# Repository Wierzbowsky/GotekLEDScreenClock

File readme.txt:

--------------------------------------------------------------------------------
Clock with calendar from Gotek's LED screen parts
Copyright (c) 2022-2023 Wierzbowsky [RBSC]
Version 1.0.0005
--------------------------------------------------------------------------------

About
-----

This is the the self-made clock that was created from salvaged Gotek's 7-segment LED screen boards. The original Gotek
screen boards need to be dismantled and all parts (IC, screen, capacitor) are used to create a single or combined
indicator panel with the help of tiny circuit boards that can be joined together. These boards share all signals except
for DIO. Each DIO pin is connected to the corresponding pin of the Arduino Mini, Nano or Uno board. This particular clock
has 6 screens joined together.

The screens can display decimal and hexadecimal numbers with or without prepending zeroes, single digits and characters
at defined positions, all Latin alphabet and also several special characters (minus, plus, slash, etc). The original
Arduino library for the TM1651 chip created by Derek Cooper was almost completely rewritten and enriched with features.
A few subroutines from the library were imported into the .INO file to make things easier.

The Arduino board with the custom self-made firmware allows to set the time and date, select 3 brightness levels and also
to enable the auto-brightness mode. A user can enable the hourly beep during day hours and set the adjustment to slow
down or make the clock run faster. The total consumption of the clock with Arduino board is around 100mA, so powering it
up from a USB2 port is fine.

Assembling
----------

Take 6 orginal Gotek LED screen boards and desolder the LED screen, the controller chip and the capacitor. The solder the
chip, capacitor and the screen onto the small board (you can order it from jlcpcb.com factory using the provided Gerber
files).

Solder a 4-pin single row header to the right side of one assembled board. To make it easier, it's recommended to solder
the 4-pin header BEFORE soldering the screen. Cut the popping out pins of the pin header from the other side so that the
screen could be fully set onto the board.

Assemble the 2-row 3-column display from the 6 complete boards. Make sure that there's no gap between the screens. To join
the boards you can use U shaped pins cut from the pin headers. See the picture of the assembled screen for reference.

Connect power, ground and clock lines of each screens in a row together. Solder 3 wires between corresponding solder pads
of power, ground and clock signals of the upper row and the bottom row. See the picture of the assembled screen.

Finally, solder four 2-pin headers onto the DIO solder pads of each board. 

Connections
-----------

Connect each board's DIO pin to the digitap I/O pin of the Arduino Uno or Nano board. Please note thet the board has DIO
pads on each side, so please connect only ONE of them (one DIO signal for each screen). Connecting the DIO pins should be
done in the specific order so that the pin the the smallest number is connected to the leftmost screen.

In my setup the DIO pins are connected to the Arduino board the following way:

-------------------------
|---3---|---4---|---5---|
-------------------------
|---6---|---7---|---8---|
-------------------------

Connect the 3.3v power from the Arduino board to the 4-pin header's VCC pin. Connect the ground from the Arduino board to
the 4-pin header's GND pin. Connect the I/O pin 3 from the Arduino board to the 4-pin header's CLK pin (this is clock
signal). You can change the pin assignment in the source files if you wish. The current pin assignment is as follows:

Arduino		Clock board or beeper/button
--------------------------------------------
3.3v		VCC
GND		GND
 2		CLK
 3		DIO pin of screen 1
 4		DIO pin of screen 2
 5		DIO pin of screen 3
 6		DIO pin of screen 4
 7		DIO pin of screen 5
 8		DIO pin of screen 6
12		Beeper (optional)
13		Button
GND		Beeper's ground
GND             Button's ground

The piezo beeper is optional, but recommended. You can use a simple 2-pin beeper in a barrel-shaped case. It can be found
anywhere on AliExpress or Ebay. For example: https://www.ebay.com/itm/374210416844

Operation
---------

The clock is controlled by a single pushbutton. There are 3 types of commands that you can execute. A short pushdown (less
than 1 second push), a medium pushdown (over 1 second push) and a long pushdown (over 2 second push). It's all about timing.
Each operation is acknowledged by the clock with a beep of different frequency and duration if beep is enabled.

When the clock shows date and time, a short pushdown will change the brightness mode and disable the auto-brightness mode if
if was previously set. There are 3 different brightness levels to select manually. The auto-brightness uses only the dimmest
and the brightest levels.

The medium pushdown will allow to enter the settings mode (see below). The long pushdown switches on the auto-brightness
mode. The brightness will automatically change based on time of the day. From 8:00 to 20:00 high brightness is set,
otherwise low brightness is set.

The settings option can be selected by holding the pushbutton for over 1 second. In the settings mode a short pushdown will
change the value of hour, minute, second (reset to zero), day, month, year, select beep ON or beep OFF, select auto-brightness
ON of OFF, as well as allow to set the clock speed adjustment in the range of -15 to 15 (slow/fast). A short pushdown will
zero the value of seconds if seconds are blinking, for other values it will either switch them between ON or OFF or advance
the setting by 1. The medium pushdown will allow to select the setting that needs to be changed (hour, minute, day, etc.).
The currently selected value will blink. The selection is done in a loop, for example: second->minute->hour->second. The long
pushdown will switch to the next setup screen. That last screen of the setup will ask to press a button to start the clock
with the selected settings. The following setup screens are available in version 1.0.0005:

-> Set time -> Set date -> Set auto-brightness -> Set beep -> Set adjust -> Start clock

It may be tricky to change settings for the first time, but you will get used to it pretty fast.

Operation and test videos
-------------------------

You can see the videos of the clock's testing on Youtube:

 - https://www.youtube.com/watch?v=1-ujJE8o4cY
 - https://www.youtube.com/watch?v=EFognT4_trQ

IMPORTANT!
----------

I provide all files and information for free, without any liability (see the disclaimer.txt file). The provided information,
software or hardware must not be used for commercial purposes unless permitted by the owner. Producing a small amount of
bare boards for personal projects and selling the rest of the batch is allowed without the permission.

When the sources files are used to create alternative projects, please always mention the original source and the copyright!

Contact information
-------------------

The members of RBSC group Tnt23, Wierzbowsky, Pyhesty, Ptero, GreyWolf, SuperMax, VWarlock and DJS3000 can be contacted via the group's e-mail
address:

info@rbsc.su

The group's coordinator could be reached via this e-mail address:

admin@rbsc.su

The group's website can be found here:

https://rbsc.su/
https://rbsc.su/ru

The RBSC's hardware repository can be found here:

https://github.com/rbsc

The RBSC's 3D model repository can be found here:

https://www.thingiverse.com/groups/rbsc/things

-= ! MSX FOREVER ! =-

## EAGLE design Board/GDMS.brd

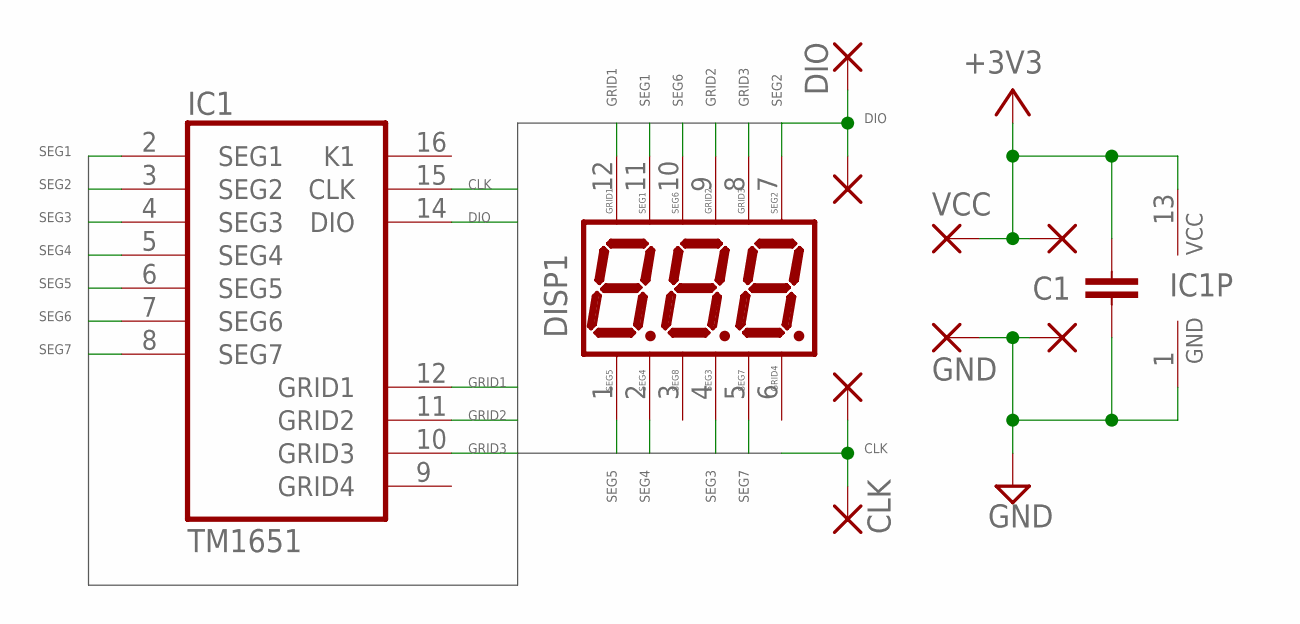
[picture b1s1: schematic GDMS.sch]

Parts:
C1: 100nF; C0805
DIS1: SP410312N; 3D7SEG
IC1: TM1651; SO16
P1: VCC; PADTH
P2, P4, P8, P9: PADTH
P3: GND; PADTH
P7: CLK; PADTH
P10: DIO; PADTH

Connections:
+3V3: C1.1, IC1.13 (VCC), P1.1, P2.1
CLK: IC1.15 (CLK), P7.1, P8.1
DIO: IC1.14 (DIO), P9.1, P10.1
GND: C1.2, IC1.1 (GND), P3.1, P4.1
GRID1: DIS1.12 (GRID1), IC1.12 (GRID1)
GRID2: DIS1.9 (GRID2), IC1.11 (GRID2)
GRID3: DIS1.8 (GRID3), IC1.10 (GRID3)
SEG1: DIS1.11 (SEG1), IC1.2 (SEG1)
SEG2: DIS1.7 (SEG2), IC1.3 (SEG2)
SEG3: DIS1.4 (SEG3), IC1.4 (SEG3)
SEG4: DIS1.2 (SEG4), IC1.5 (SEG4)
SEG5: DIS1.1 (SEG5), IC1.6 (SEG5)
SEG6: DIS1.10 (SEG6), IC1.7 (SEG6)
SEG7: DIS1.5 (SEG7), IC1.8 (SEG7)

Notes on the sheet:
DISP1

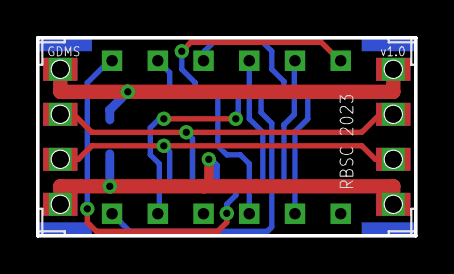
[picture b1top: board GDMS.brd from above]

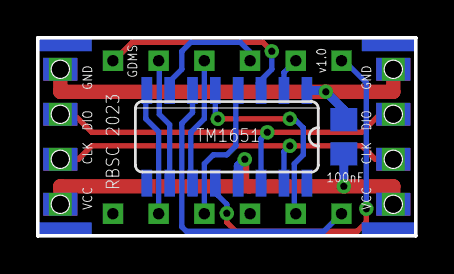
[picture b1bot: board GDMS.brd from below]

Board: 2 copper layers, 21.0 x 11.0 mm, 11 parts (2 on the bottom side), 14 nets.

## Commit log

2023-03-04 :confetti_ball: Added .gitattributes & .gitignore files
2023-03-04 Initial release 04.03.2023
    Initial release
2023-10-09 Updated firmware
    Firmware has been updated for more precise clock adjustment, added title with version number and build, also added waiting for a button press to start the clock after adjustments.
2023-10-28 Updated to version 1.0.0005
    Added auto-brightness control. Beep setting is now global and off by default. Core was rewritten to prevent lockups.
2023-10-31 Version 1.00.0006
    More stable build, picture of the case added.
2023-11-05 Version 1.0.0007
    Decreased the multiplier's value for better clock correction precision
2024-01-01 Updated 01.01.2024
    Fixed a typo in readme
